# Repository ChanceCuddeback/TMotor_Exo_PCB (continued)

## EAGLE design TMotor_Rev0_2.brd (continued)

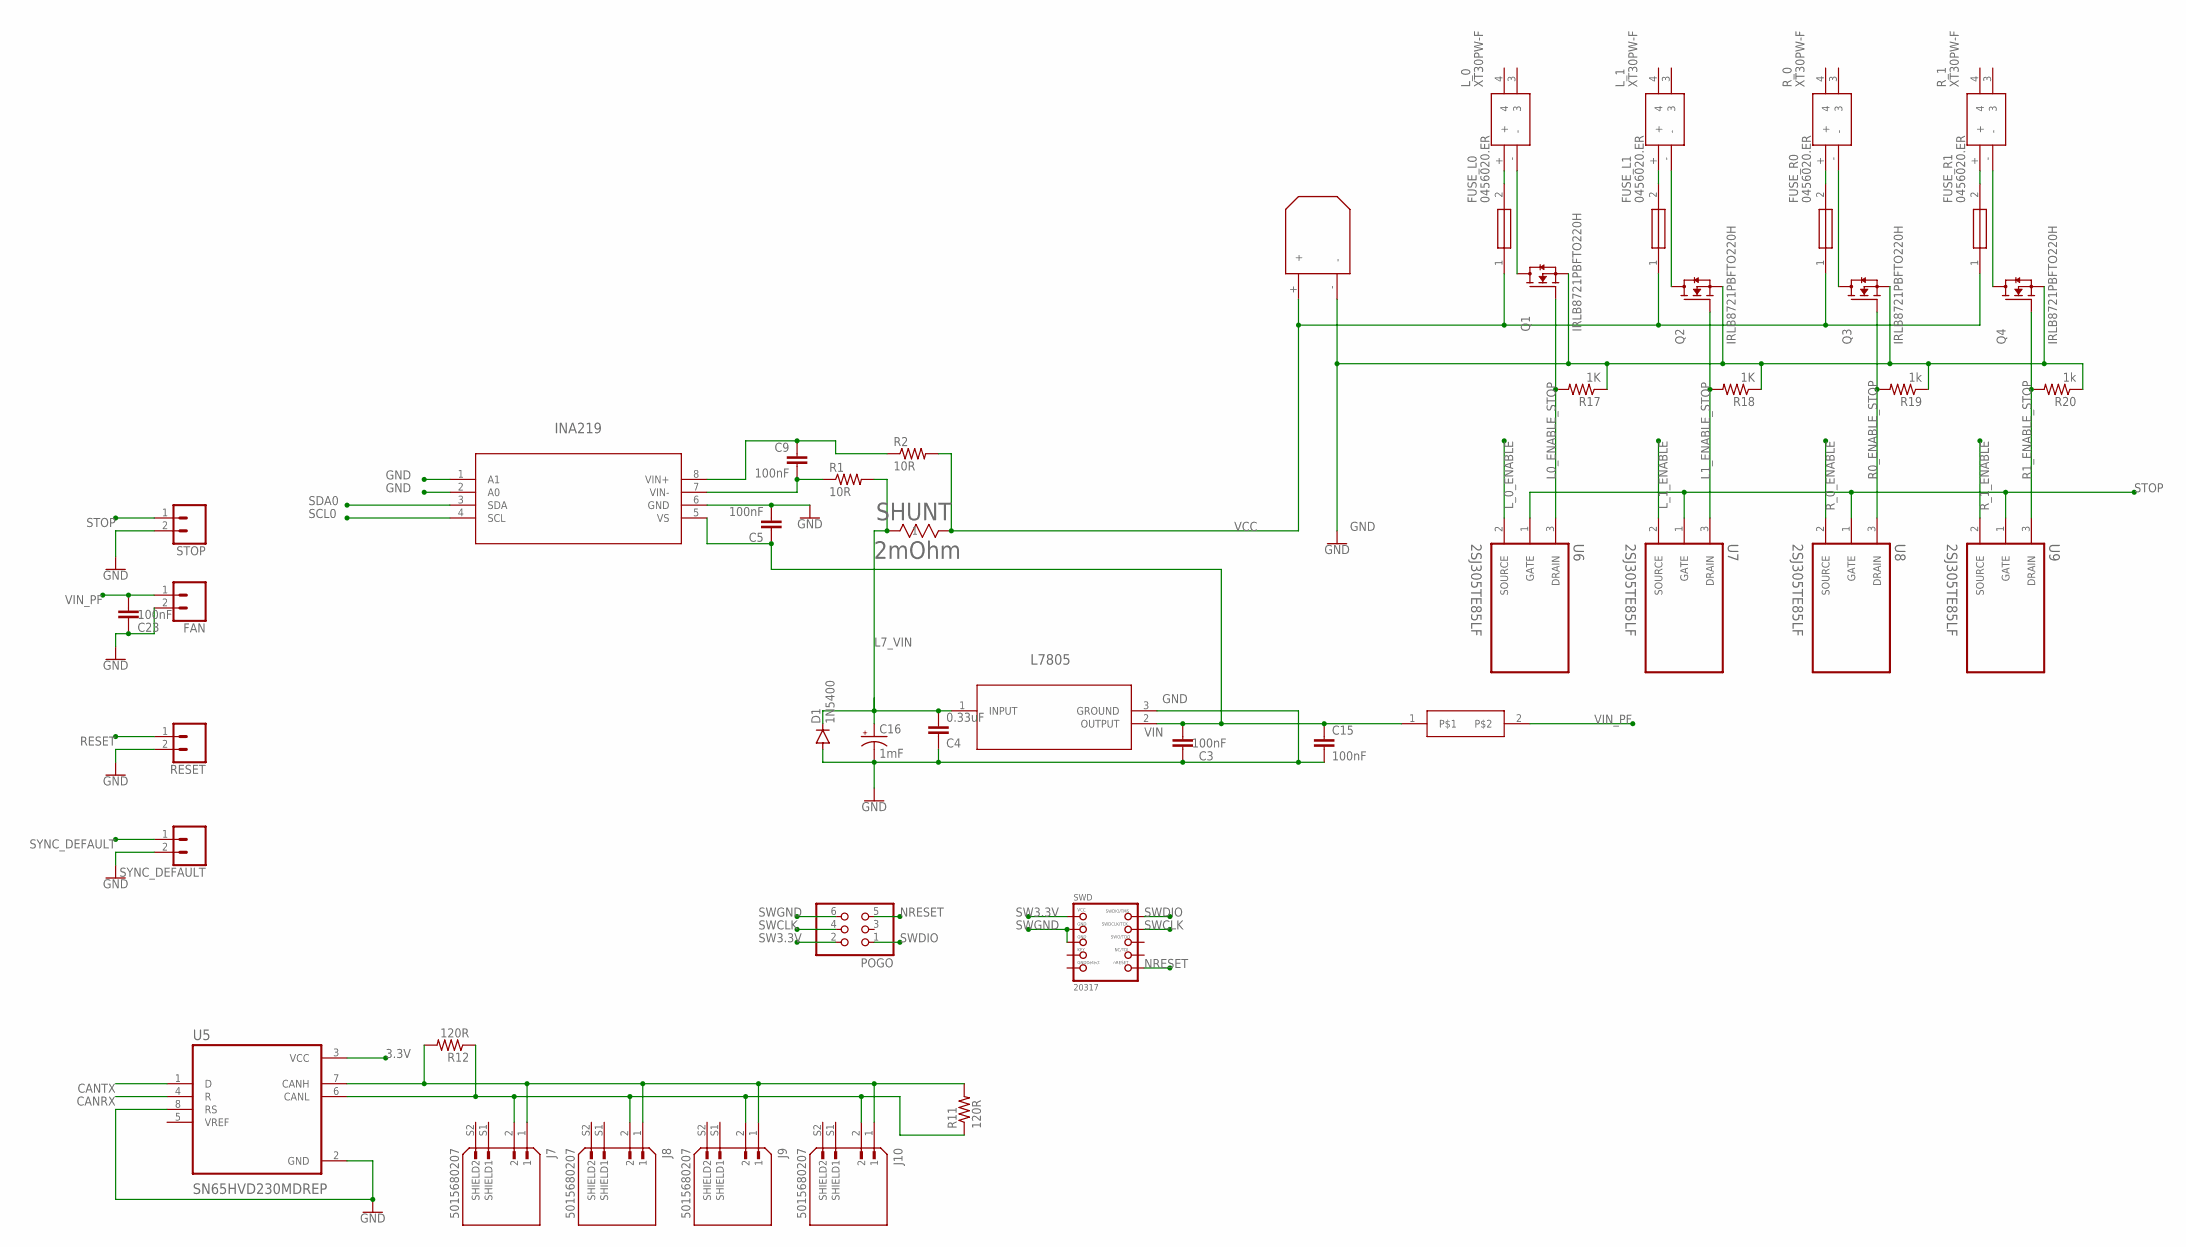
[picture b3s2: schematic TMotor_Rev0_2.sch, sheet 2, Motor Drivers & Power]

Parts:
C3, C5, C9, C15, C23: 100nF; C050-024X044
C4: 0.33uF; C050-024X044
C16: 1mF; E5-10,5
D1: 1N5400; DO201-15
FAN: CONN_02; 1X02
FUSE_L0, FUSE_L1: 0456020.ER; FUSC10131X312N
FUSE_R0, FUSE_R1: 0456020.ER; FUSC10131X312N
INA219: D8_TEX
J7, J8, J9, J10: 5015680207; MOLEX_5015680207
L7805: DPAK_STM
L_0, L_1: XT30PW-F; XT30PWF
POGO: PINHD-2X3; 2X03
Q1, Q2, Q3, Q4: IRLB8721PBFTO220H; TO220H
R1, R2: 10R; 0207/10
R11, R12: 120R; 0207/10
R17, R18: 1K; 0207/10
R19, R20: 1k; 0207/10
RESET: CONN_02; 1X02
R_0, R_1: XT30PW-F; XT30PWF
SHUNT: 2mOhm; STA_CSNL2512(2)_STP
STOP: CONN_02; 1X02
SWD: 20317; 2X05_1.27MM_BOX_POSTS
SYNC_DEFAULT: CONN_02; 1X02
U5: SN65HVD230MDREP; SOIC127P599X175-8N
U6, U7, U8, U9: 2SJ305TE85LF; TRANS_SSM3J325F,LF
U$6: 0458002.DR; FUSE_LITTEL_448
U$9: XT30; XT30_HORIZONTAL

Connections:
3.3V: U5.3 (VCC); also elsewhere on the board
CANRX: U5.4 (R); also elsewhere on the board
CANTX: U5.1 (D); also elsewhere on the board
GND: C3.1, C4.1, C5.2, C15.2, C16.-, C23.1, D1.A, FAN.2, INA219.1 (A1), INA219.2 (A0), INA219.6 (GND), L7805.3 (GROUND), Q1.3 (S), Q2.3 (S), Q3.3 (S), Q4.3 (S), R17.1, R18.1, R19.1, R20.1, RESET.2, STOP.2, SYNC_DEFAULT.2, U5.2 (GND), U5.8 (RS), U$9.-; also elsewhere on the board
L0_ENABLE_STOP: Q1.1 (G), R17.2, U6.3 (DRAIN)
L1_ENABLE_STOP: Q2.1 (G), R18.2, U7.3 (DRAIN)
L7_VIN: C4.2, C16.+, D1.C, L7805.1 (INPUT), R1.2, SHUNT.1
L_0_ENABLE: U6.2 (SOURCE); also elsewhere on the board
L_1_ENABLE: U7.2 (SOURCE); also elsewhere on the board
unnamed: C9.1, INA219.8 (VIN+), R2.1
unnamed: C9.2, INA219.7 (VIN-), R1.1
unnamed: FUSE_L0.2, L_0.+
unnamed: J7.1, J8.1, J9.1, J10.1, R11.2, R12.2, U5.7 (CANH)
unnamed: J7.2, J8.2, J9.2, J10.2, R11.1, R12.1, U5.6 (CANL)
unnamed: FUSE_L1.2, L_1.+
unnamed: FUSE_R1.2, R_1.+
unnamed: FUSE_R0.2, R_0.+
unnamed: L_0.-, Q1.2 (D)
unnamed: Q3.2 (D), R_0.-
unnamed: Q4.2 (D), R_1.-
unnamed: L_1.-, Q2.2 (D)
NRESET: POGO.5, SWD.10 (NRESET)
R0_ENABLE_STOP: Q3.1 (G), R19.2, U8.3 (DRAIN)
R1_ENABLE_STOP: Q4.1 (G), R20.2, U9.3 (DRAIN)
RESET: RESET.1; also elsewhere on the board
R_0_ENABLE: U8.2 (SOURCE); also elsewhere on the board
R_1_ENABLE: U9.2 (SOURCE); also elsewhere on the board
SCL0: INA219.4 (SCL); also elsewhere on the board
SDA0: INA219.3 (SDA); also elsewhere on the board
STOP: STOP.1, U6.1 (GATE), U7.1 (GATE), U8.1 (GATE), U9.1 (GATE); also elsewhere on the board
SW3.3V: POGO.2, SWD.1 (VCC)
SWCLK: POGO.4, SWD.4 (SWDCLK)
SWDIO: POGO.1, SWD.2 (SWDIO)
SWGND: POGO.6, SWD.3 (GND), SWD.5 (GND)
SYNC_DEFAULT: SYNC_DEFAULT.1; also elsewhere on the board
VCC: FUSE_L0.1, FUSE_L1.1, FUSE_R0.1, FUSE_R1.1, R2.2, SHUNT.2, U$9.+
VIN: C3.2, C5.1, C15.1, INA219.5 (VS), L7805.2 (OUTPUT), U$6.1
VIN_PF: C23.2, FAN.1, U$6.2; also elsewhere on the board

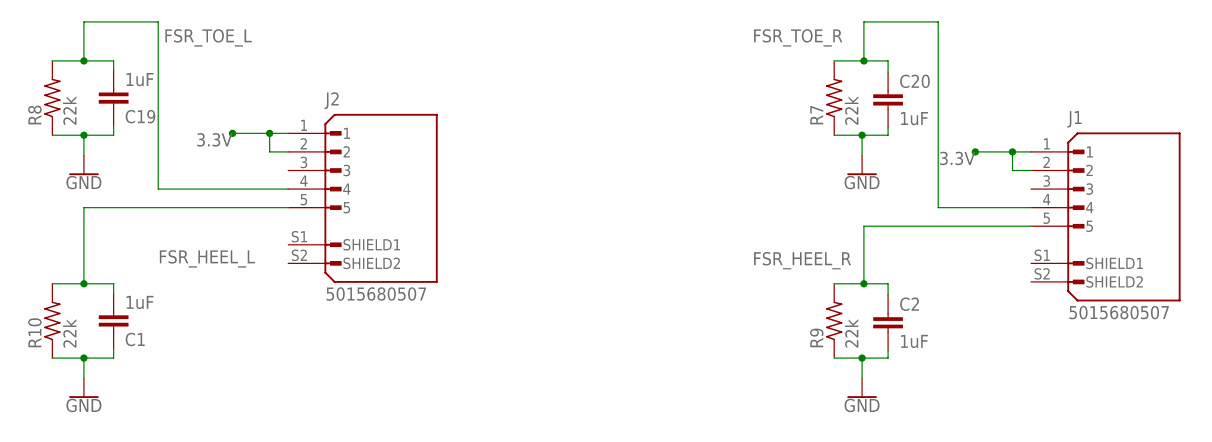
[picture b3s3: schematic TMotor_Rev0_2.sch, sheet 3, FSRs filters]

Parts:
C1, C2, C19, C20: 1uF; C050-024X044
J1, J2: 5015680507; MOLEX_5015680507
R7, R8, R9, R10: 22k; 0207/10

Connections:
3.3V: J1.1, J1.2, J2.1, J2.2; also elsewhere on the board
FSR_HEEL_L: C1.2, J2.5, R10.2; also elsewhere on the board
FSR_HEEL_R: C2.1, J1.5, R9.2; also elsewhere on the board
FSR_TOE_L: C19.2, J2.4, R8.2; also elsewhere on the board
FSR_TOE_R: C20.1, J1.4, R7.2; also elsewhere on the board
GND: C1.1, C2.2, C19.1, C20.2, R7.1, R8.1, R9.1, R10.1; also elsewhere on the board

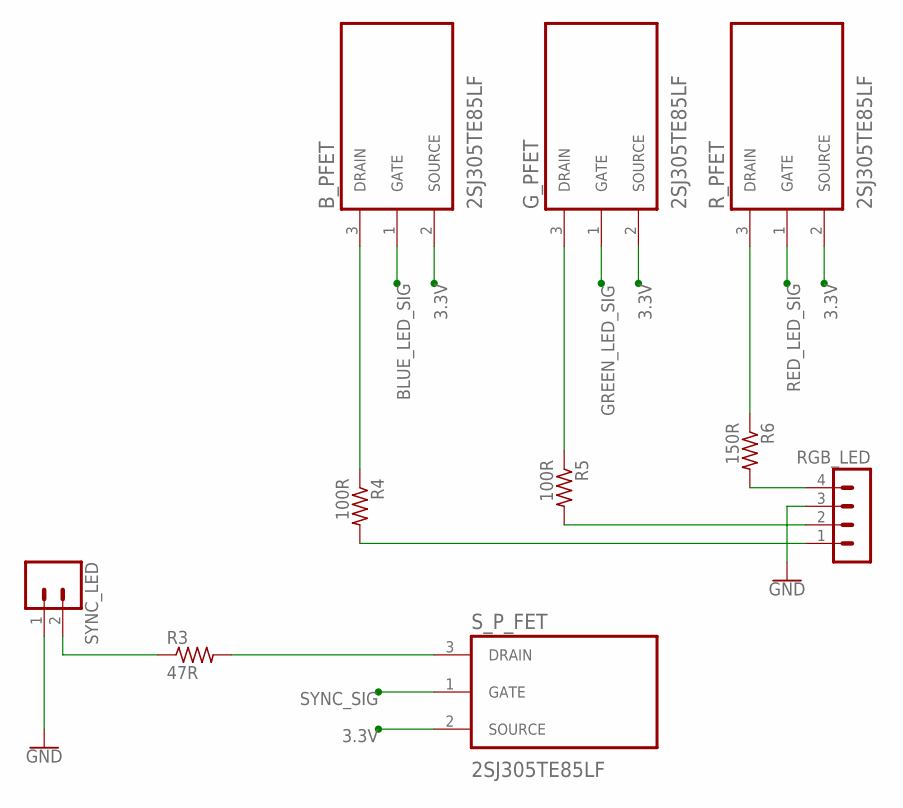
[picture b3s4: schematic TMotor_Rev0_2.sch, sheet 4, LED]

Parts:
B_PFET: 2SJ305TE85LF; TRANS_SSM3J325F,LF
G_PFET: 2SJ305TE85LF; TRANS_SSM3J325F,LF
R3: 47R; 0207/10
R4, R5: 100R; 0207/10
R6: 150R; 0207/10
RGB_LED: MA04-1
R_PFET: 2SJ305TE85LF; TRANS_SSM3J325F,LF
SYNC_LED: CONN_02; 1X02
S_P_FET: 2SJ305TE85LF; TRANS_SSM3J325F,LF

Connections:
3.3V: B_PFET.2 (SOURCE), G_PFET.2 (SOURCE), R_PFET.2 (SOURCE), S_P_FET.2 (SOURCE); also elsewhere on the board
BLUE_LED_SIG: B_PFET.1 (GATE); also elsewhere on the board
GND: RGB_LED.3, SYNC_LED.1; also elsewhere on the board
GREEN_LED_SIG: G_PFET.1 (GATE); also elsewhere on the board
unnamed: R4.2, RGB_LED.1
unnamed: B_PFET.3 (DRAIN), R4.1
unnamed: R3.2, S_P_FET.3 (DRAIN)
unnamed: R3.1, SYNC_LED.2
unnamed: R6.2, RGB_LED.4
unnamed: R5.2, RGB_LED.2
unnamed: G_PFET.3 (DRAIN), R5.1
unnamed: R6.1, R_PFET.3 (DRAIN)
RED_LED_SIG: R_PFET.1 (GATE); also elsewhere on the board
SYNC_SIG: S_P_FET.1 (GATE); also elsewhere on the board

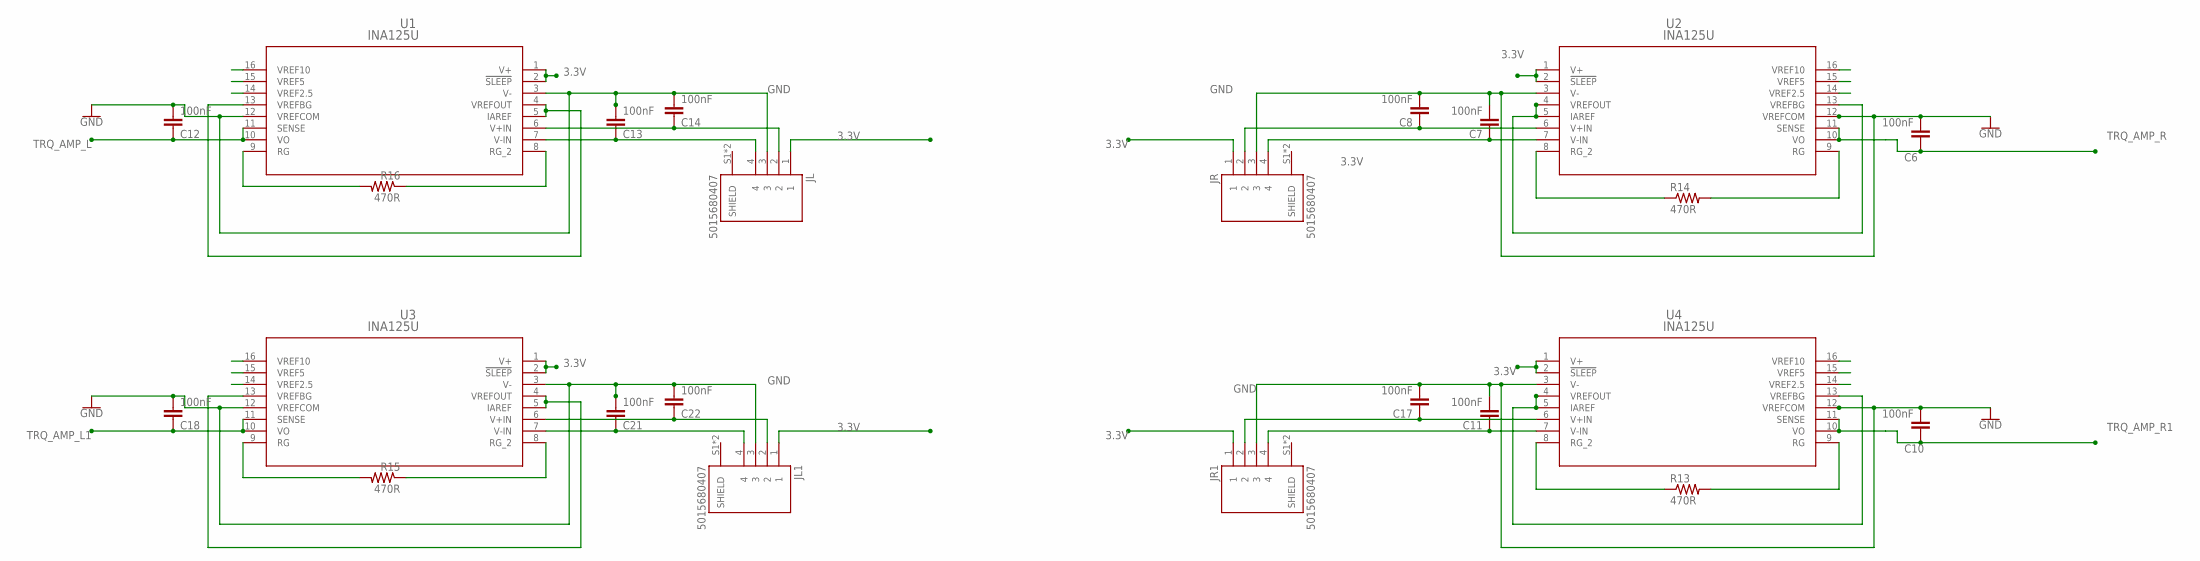
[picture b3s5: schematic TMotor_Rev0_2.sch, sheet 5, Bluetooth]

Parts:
C6, C7, C8, C10, C11, C12, C13, C14, C17, C18, C21, C22: 100nF; C050-024X044
JL, JL1: 5015680407; MOLEX_5015680407
JR, JR1: 5015680407; MOLEX_5015680407
R13, R14, R15, R16: 470R; 0207/10
U1, U2, U3, U4: INA125U; D16

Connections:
3.3V: JL.1, JL1.1, JR.1, JR1.1, U1.1 (V+), U1.2 (!SLEEP), U2.1 (V+), U2.2 (!SLEEP), U3.1 (V+), U3.2 (!SLEEP), U4.1 (V+), U4.2 (!SLEEP); also elsewhere on the board
GND: C6.2, C7.2, C8.2, C10.2, C11.2, C12.2, C13.2, C14.2, C17.2, C18.2, C21.2, C22.2, JL.3, JL1.3, JR.3, JR1.3, U1.3 (V-), U1.12 (VREFCOM), U2.3 (V-), U2.12 (VREFCOM), U3.3 (V-), U3.12 (VREFCOM), U4.3 (V-), U4.12 (VREFCOM); also elsewhere on the board
unnamed: U1.4 (VREFOUT), U1.5 (IAREF), U1.13 (VREFBG)
unnamed: U2.4 (VREFOUT), U2.5 (IAREF), U2.13 (VREFBG)
unnamed: R14.1, U2.8 (RG_2)
unnamed: R14.2, U2.9 (RG)
unnamed: C8.1, JR.2, U2.6 (V+IN)
unnamed: C7.1, JR.4, U2.7 (V-IN)
unnamed: C14.1, JL.2, U1.6 (V+IN)
unnamed: C13.1, JL.4, U1.7 (V-IN)
unnamed: R16.2, U1.9 (RG)
unnamed: R16.1, U1.8 (RG_2)
unnamed: U4.4 (VREFOUT), U4.5 (IAREF), U4.13 (VREFBG)
unnamed: R13.1, U4.8 (RG_2)
unnamed: R13.2, U4.9 (RG)
unnamed: C17.1, JR1.2, U4.6 (V+IN)
unnamed: C11.1, JR1.4, U4.7 (V-IN)
unnamed: U3.4 (VREFOUT), U3.5 (IAREF), U3.13 (VREFBG)
unnamed: C22.1, JL1.2, U3.6 (V+IN)
unnamed: C21.1, JL1.4, U3.7 (V-IN)
unnamed: R15.2, U3.9 (RG)
unnamed: R15.1, U3.8 (RG_2)
TRQ_AMP_L: C12.1, U1.10 (VO), U1.11 (SENSE); also elsewhere on the board
TRQ_AMP_L1: C18.1, U3.10 (VO), U3.11 (SENSE); also elsewhere on the board
TRQ_AMP_R: C6.1, U2.10 (VO), U2.11 (SENSE); also elsewhere on the board
TRQ_AMP_R1: C10.1, U4.10 (VO), U4.11 (SENSE); also elsewhere on the board

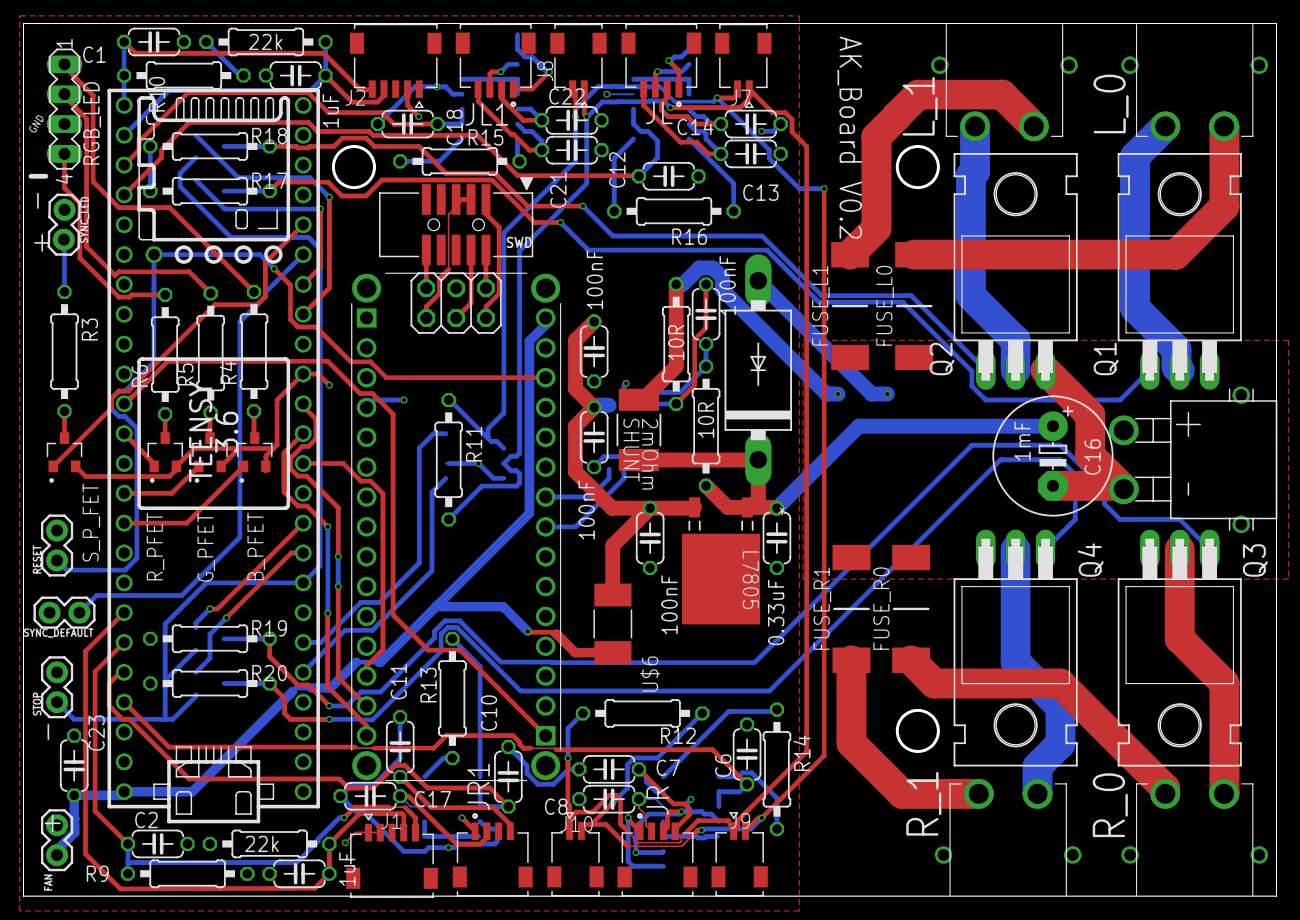
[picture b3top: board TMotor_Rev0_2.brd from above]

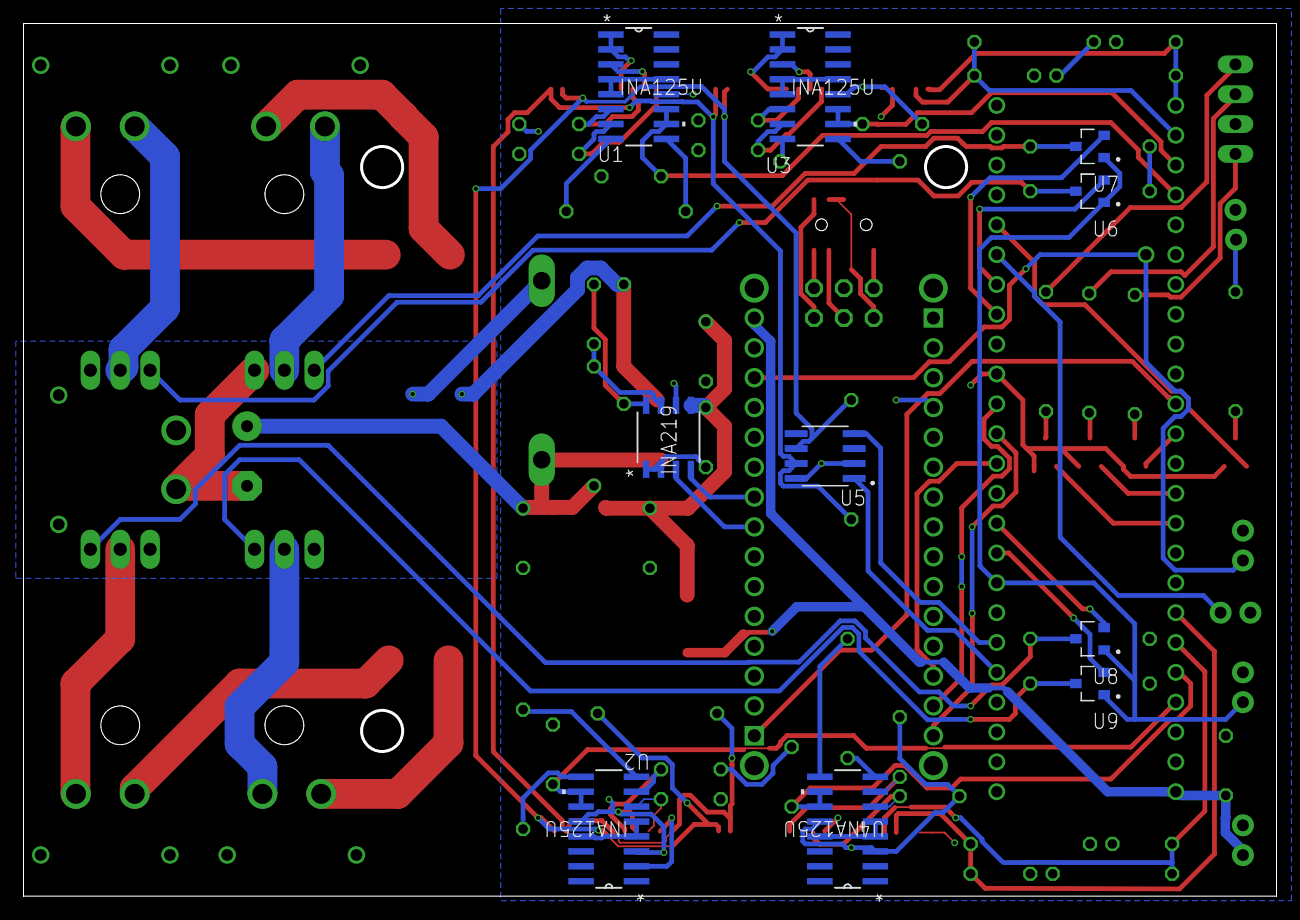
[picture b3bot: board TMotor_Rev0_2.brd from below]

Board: 2 copper layers, 106.4 x 74.0 mm, 94 parts (10 on the bottom side), 82 nets.

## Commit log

2021-10-13 Added sch and brd files
2021-10-16 Deleted motor drivers, headers and old connectors.
2021-10-19 Pre check completion, with pogo pins
2021-10-20 Post DRC, pre ground plane modifications
2021-10-21 Rearranged pre ground plane pour
2021-10-21 Post ground plane and DRC
2021-10-26 Fixed power electronics, pre Paul PCB changes.
2021-10-26 Forgot to save haha
2021-10-27 Added silkscreen and finalized design
2021-10-28 Final V0 sent to oshpark
2021-12-09 Created quad board CAN board with both the Teensy and Nano.
2022-02-03 cross connected the spi coms pins due to TSPISlave function
2022-02-04 updated LED power
2022-02-16 changed RGB LED to PWM
2022-02-16 removed recovery files
2022-02-16 added gitignore to ignore recovery files
2022-02-16 created CIPO COPI transfer spot
2022-02-16 repositioned headers for switches
2022-03-04 added fuses and fets for motor power
2022-03-07 added motor fets to top level
2022-03-08 Added Estop to motor power circuit
2022-03-08 Updated resistor value on motor stop pulldown
2022-03-10 rerouted some traces for motor power
2022-03-25 Restricted area over CAN
2022-04-05 updated board to use Teensy 4.1
2022-06-03 Updated motor cutoff, added test points
2022-06-03 removed old files
2022-06-07 fixed typo in rev 0.1
2022-06-13 First Rev1 changes
2022-06-14 Rev1 Final chance
2022-06-14 Incremented Version number
2022-09-01 fixed 5v regulator in rev 0.41
2022-09-06 Added integrated PCB version w/ MCP25625
2023-01-12 Updated File names
2023-01-12 Removed Power FETS, power FET supporting hardware, and SWD IO for nano
2023-01-17 Added serial connection between nano and teensy
2023-01-18 Added Upright Power connectors
2023-01-19 Arranged new connectors
2023-01-19 Passed DRC check. Need to perform a more rigorous manual review.
2023-01-23 Post review
2023-01-23 Test
2023-01-24 Comments added.
2023-02-01 This version of the board (0.5.1) is based on the version Chance worked on. Changes are made to incorporate the following needs: (1) Remove one torque sensor connector and its related components from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
2023-03-20 Embed the I2C connections between Teensy and Nano.
    Other edits include: Improved motor power traces. Tried to improve the traces around the CAN traces, the target is to reduce the CAN signal rise time. Improved the placement of multiple components. R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
2023-03-21 GND and 3.3V trace widths (copper pour) improved.
2023-03-21 Improved CAN bus termination resistor placement
2023-03-21 Replaced the CAN transceiver
    Replaced SN65HVD230MDREP with SN65HVD230DR
